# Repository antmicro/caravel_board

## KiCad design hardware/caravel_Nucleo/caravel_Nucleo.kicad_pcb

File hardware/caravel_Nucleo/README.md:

# Caravel Nucleo

### Overview

This repository contains open hardware design files for a expansion board compatible with [STM32 Nucleo-144 boards](https://www.st.com/en/evaluation-tools/stm32-nucleo-boards.html).\
This board connects IO signals from the STM32 MCU located on the Nucleo-144 board to an open hardware [Caravel](https://github.com/efabless/caravel_board).\
The Caravel breakout board allows testing ASIC designs prepared for Multi Project Wafer (MPW) shuttles and fabricated with one of the available open Process Design Kits (PDKs).

You can learn more about Open Shuttle Program by visiting this [link](https://efabless.com/open_shuttle_program).

The Caravel Nucleo board routes the interfaces from Caravel and provides the necessary power buses.
The design files were prepared in KiCad 6. This design is currently a Work in Progress (WiP).

## Project structure

The main repository directory contains KiCad PCB project files, and a README.
The remaining files are stored in the following directories:

* `lib` - contains the KiCad 6 component libraries
* `doc` - contains generated schematics and other documentation
* `img` - contains graphics for this README

## Key features

* Caravel-breakout testbed slot with optional FlexyPins
* `ST morpho` compatible
* USB for MPRJ SPI/UART debug
* SPI Flash connected to Caravel and Morpho connector
* Dedicated 10MHz oscillator
* Dual LDO with fixed and I2C controlled feedback (selectable)

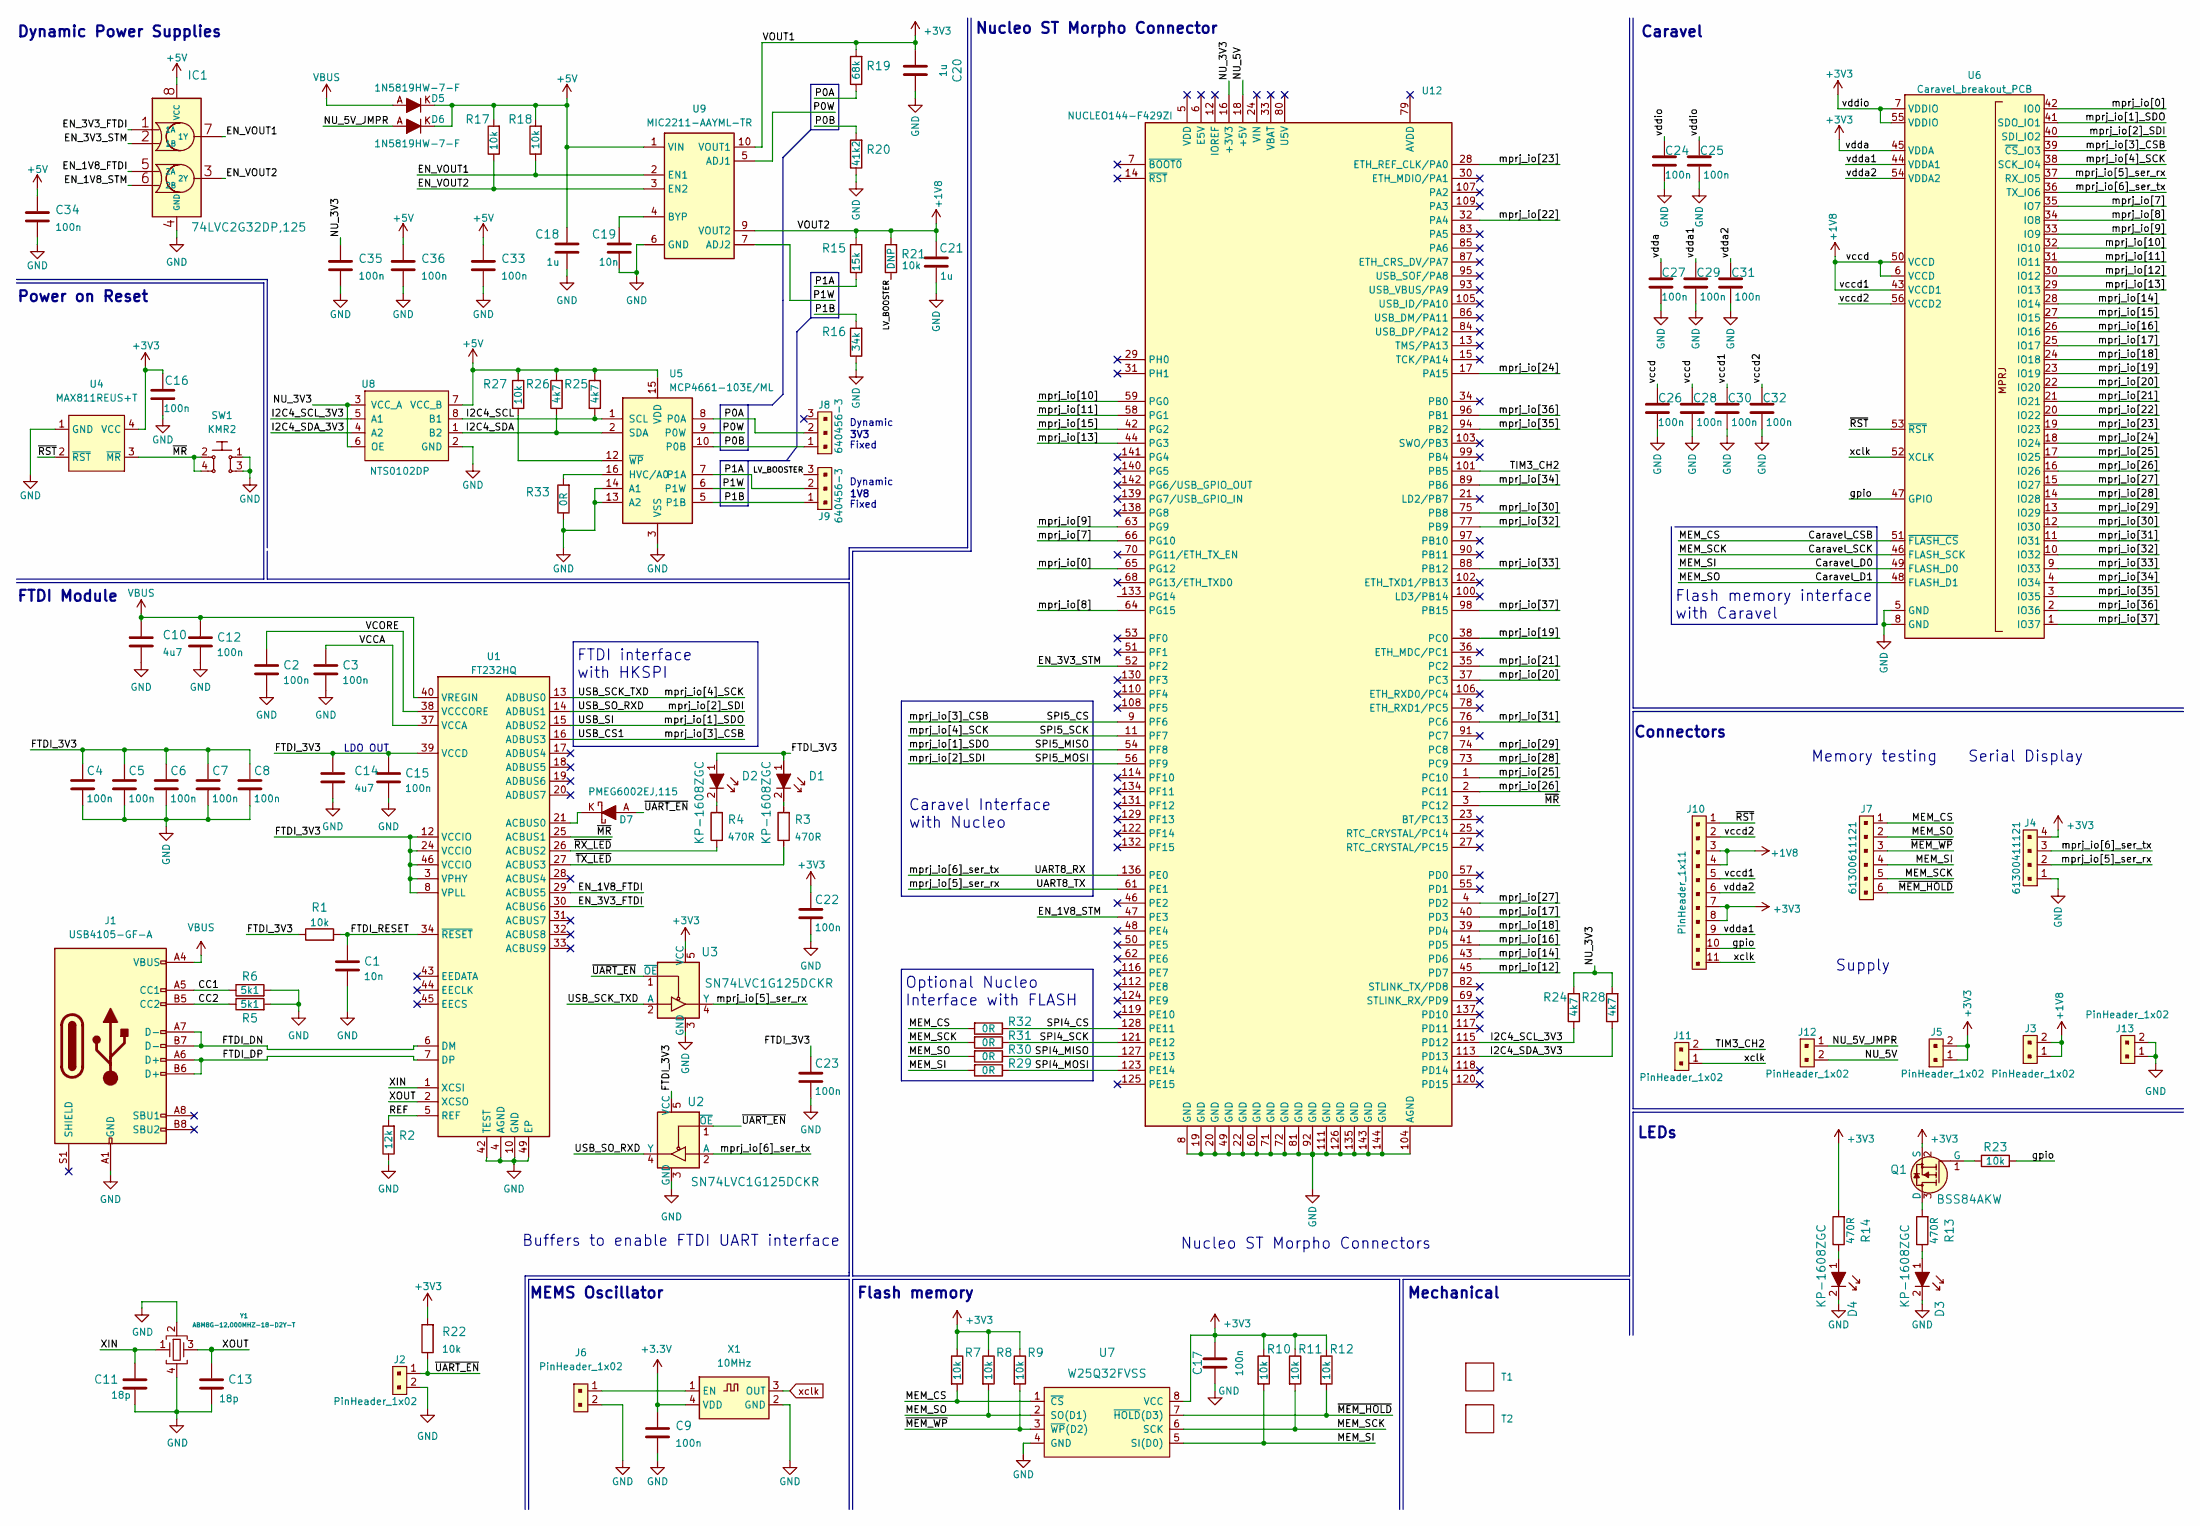
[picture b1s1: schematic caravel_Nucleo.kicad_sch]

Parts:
C1, C19: C_10n_0603; 0603-cap; MPN 06031C103JAT2A
C2, C3, C4, C5, C6, C7, C8, C9, C12, C15, C16, C17, C22, C23, C24, C25, C26, C27, C28, C29, C30, C31, C32, C33, C34, C35, C36: C_100n_0603; 0603-cap; MPN 0603YC104KAZ2A
C10, C14: C_4u7_0603; 0603-cap; MPN C1608X5R1V475M080AC
C11, C13: C_18p_0603; 0603-cap; MPN C0603C180J5GACTU
C18, C20, C21: C_1u_0603; 0603-cap; MPN 0603YD105KAT2A
D1, D2, D3, D4: KP-1608ZGC; LED_0603; MPN KP-1608EC
D5, D6: 1N5819HW-7-F; SOD-123; MPN 1N5819HW-7-F
D7: PMEG6002EJ,115; SOD-323F; MPN PMEG6002EJ,115
IC1: 74LVC2G32DP,125; TSSOP-8_W3mm; MPN 74LVC2G32DP,125
J1: USB4105-GF-A; GCT_USB4105-GF-A; MPN USB4105-GF-A
J2, J3, J5, J6, J11, J12, J13: PinHeader_1x02; PinHeader_1x2_P2.54mm; MPN M20-9990246
J4: 61300411121; PinHeader_1x4_P2.54mm_Drill1.02mm; MPN 61300411121
J7: 61300611121; MPN 61300611121
J8, J9: 640456-3; PinHeader_1x3_P2.54_Drill1.1mm; MPN 640456-3
J10: PinHeader_1x11; PinHeader_1x11_P2.54_Vertical; MPN 6-146280-1
Q1: BSS84AKW; SOT-323; MPN BSS84AKW,115
R1, R7, R8, R9, R10, R11, R12, R17, R18, R21, R22, R23, R27: R_10k_0603; 0603-res; MPN CR0603-JW-103ELF
R2: R_12k_0603; 0603-res; MPN CR0603-FX-1202ELF
R3, R4, R13, R14: R_470R_0603; 0603-res; MPN CR0603-JW-471GLF
R5, R6: R_5k1_0603; 0603-res; MPN CRCW06035K10FKEA
R15: R_15k_0603; 0603-res; MPN CR0603-FX-1502ELF
R16: R_34k_0603; 0603-res; MPN ERJ-3EKF3402V
R19: R_68k_0603; 0603-res; MPN MC0063W0603168K
R20: R_41k2_0603; 0603-res; MPN CRCW060341K2FKEA
R24, R25, R26, R28: R_4k7_0603; 0603-res; MPN CR0603-FX-4701ELF
R29, R30, R31, R32, R33: R_0R_0603; 0603-res; MPN CR0603-J/-000ELF
SW1: KMR2; SW_SPST_4.2x2.8; MPN KMR211NGLFS
T1: efabless_logo; logo
T2: efabless_logo
U1: FT232HQ; QFN-48-1EP_8x8mm_P0.5mm_EP6.2x6.2mm_FT232HQ_marking; MPN FT232HQ-TRAY
U2, U3: SN74LVC1G125DCKR; SOT-353; MPN SN74LVC1G125DCKR
U4: MAX811REUS+T; SOT-143-4; MPN MAX811REUS+T
U5: MCP4661-103E/ML; QFN-16_EP_4x4_Pitch0.65mm; MPN MCP4661103E/ML
U6: Caravel_breakout_PCB; caravel_breakout
U7: W25Q32FVSS; SOIC127P790X216-8N; MPN W25Q32FVSSIG
U8: NTS0102DP; TSSOP-8_W3mm; MPN NTS0102DP
U9: MIC2211-AAYML-TR; DFN-10-1EP_3x3mm; MPN MIC2211-AAYML-TR
U12: NUCLEO144-F429ZI; ST_Morpho_Connectors_144; MPN NUCLEO-F429ZI
X1: ECS-2520MVLC-100-BN-TR; Oscillator_SMD_ECS_2520MV-xxx-xx-4Pin_2.5x2.0mm; MPN ECS-2520MVLC-100-BN-TR
Y1: ABM8G-12.000MHZ-18-D2Y-T; KX-7; MPN ABM8G-12.000MHZ-18-D2Y-T

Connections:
+1V8: C21.1, C26.2, C28.2, C30.2, J3.1, J3.2, J10.3, J10.4, J10.5, R15.2, R21.2, U6.6 (VCCD), U6.43 (VCCD1), U6.50 (VCCD), U9.9 (VOUT2)
+5V: C18.1, C33.1, C34.1, C36.1, D5.K, D6.K, IC1.8 (VCC), R17.2, R18.2, R25.2, R26.2, R27.1, U5.15 (VDD), U8.7 (VCC_B), U9.1 (VIN)
/CC1: J1.A5 (CC1), R6.1
/CC2: J1.B5 (CC2), R5.1
/Caravel_CSB: J7.1, R7.2, R32.2, U6.51 (~FLASH_CS), U7.1 (~CS)
/Caravel_D0: J7.4, R10.2, R29.2, U6.49 (FLASH_D0), U7.5 (SI(D0))
/Caravel_D1: J7.2, R8.2, R30.2, U6.48 (FLASH_D1), U7.2 (SO(D1))
/Caravel_SCK: J7.5, R11.2, R31.2, U6.46 (FLASH_SCK), U7.6 (SCK)
/EN_1V8_FTDI: IC1.5 (2A), U1.29 (ACBUS5)
/EN_1V8_STM: IC1.6 (2B), U12.47 (PE3)
/EN_3V3_FTDI: IC1.1 (1A), U1.30 (ACBUS6)
/EN_3V3_STM: IC1.2 (1B), U12.52 (PF2)
/EN_VOUT1: IC1.7 (1Y), R18.1, U9.2 (EN1)
/EN_VOUT2: IC1.3 (2Y), R17.1, U9.3 (EN2)
/FTDI_3V3: C4.1, C5.1, C6.1, C7.1, C8.1, C14.1, C15.2, C23.1, D1.1, D2.1, R1.1, U1.3 (VPHY), U1.8 (VPLL), U1.12 (VCCIO), U1.24 (VCCIO), U1.39 (VCCD), U1.46 (VCCIO), U2.5 (VCC)
/FTDI_DN: J1.A7 (D-), J1.B7 (D-), U1.6 (DM)
/FTDI_DP: J1.A6 (D+), J1.B6 (D+), U1.7 (DP)
/FTDI_RESET: C1.1, R1.2, U1.34 (~RESET)
/I2C4_SCL: R25.1, U5.1 (SCL), U8.8 (B1)
/I2C4_SCL_3V3: R24.1, U8.5 (A1), U12.115 (PD12)
/I2C4_SDA: R26.1, U5.2 (SDA), U8.1 (B2)
/I2C4_SDA_3V3: R28.1, U8.4 (A2), U12.113 (PD13)
/LV_BOOSTER: J9.3, R21.1
/NU_3V3: C35.1, R24.2, R28.2, U8.3 (VCC_A), U8.6 (OE), U12.16 (+3V3)
/NU_5V: J12.2, U12.18 (+5V)
/NU_5V_JMPR: D6.A, J12.1
/P0A: J8.2, R19.1, U5.8 (P0A)
/P0B: J8.1, R20.2, U5.10 (P0B)
/P0W: U5.9 (P0W), U9.5 (ADJ1)
/P1A: J9.2, R15.1, U5.7 (P1A)
/P1B: J9.1, R16.2, U5.5 (P1B)
/P1W: U5.6 (P1W), U9.7 (ADJ2)
/REF: R2.2, U1.5 (REF)
/SPI4_CS: R32.1, U12.128 (PE11)
/SPI4_MISO: R30.1, U12.127 (PE13)
/SPI4_MOSI: R29.1, U12.123 (PE14)
/SPI4_SCK: R31.1, U12.121 (PE12)
/SPI5_CS: U1.16 (ADBUS3), U6.39 (~CS_IO3), U12.9 (PF6)
/SPI5_MISO: U1.15 (ADBUS2), U6.41 (SDO_IO1), U12.54 (PF8)
/SPI5_MOSI: U1.14 (ADBUS1), U2.4 (Y), U6.40 (SDI_IO2), U12.56 (PF9)
/SPI5_SCK: U1.13 (ADBUS0), U3.2 (A), U6.38 (SCK_IO4), U12.11 (PF7)
/TIM3_CH2: J11.2, U12.101 (PB5)
/UART8_RX: J4.3, U2.2 (A), U6.36 (TX_IO6), U12.136 (PE0)
/UART8_TX: J4.2, U3.4 (Y), U6.37 (RX_IO5), U12.61 (PE1)
/VCCA: C3.2, U1.37 (VCCA)
/VCORE: C2.2, U1.38 (VCCCORE)
/XIN: C11.1, U1.1 (XCSI), Y1.1
/XOUT: C13.1, U1.2 (XCSO), Y1.3
/gpio: J10.10, R23.2, U6.47 (GPIO)
/mprj_io[0]: U6.42 (IO0), U12.65 (PG12)
/mprj_io[7]: U6.35 (IO7), U12.66 (PG10)
/mprj_io[8]: U6.34 (IO8), U12.64 (PG15)
/mprj_io[9]: U6.33 (IO9), U12.63 (PG9)
/mprj_io[10]: U6.32 (IO10), U12.59 (PG0)
/mprj_io[11]: U6.31 (IO11), U12.58 (PG1)
/mprj_io[12]: U6.30 (IO12), U12.45 (PD7)
/mprj_io[13]: U6.29 (IO13), U12.44 (PG3)
/mprj_io[14]: U6.28 (IO14), U12.43 (PD6)
/mprj_io[15]: U6.27 (IO15), U12.42 (PG2)
/mprj_io[16]: U6.26 (IO16), U12.41 (PD5)
/mprj_io[17]: U6.25 (IO17), U12.40 (PD3)
/mprj_io[18]: U6.24 (IO18), U12.39 (PD4)
/mprj_io[19]: U6.23 (IO19), U12.38 (PC0)
/mprj_io[20]: U6.22 (IO20), U12.37 (PC3)
/mprj_io[21]: U6.21 (IO21), U12.35 (PC2)
/mprj_io[22]: U6.20 (IO22), U12.32 (PA4)
/mprj_io[23]: U6.19 (IO23), U12.28 (ETH_REF_CLK/PA0)
/mprj_io[24]: U6.18 (IO24), U12.17 (PA15)
/mprj_io[25]: U6.17 (IO25), U12.1 (PC10)
/mprj_io[26]: U6.16 (IO26), U12.2 (PC11)
/mprj_io[27]: U6.15 (IO27), U12.4 (PD2)
/mprj_io[28]: U6.14 (IO28), U12.73 (PC9)
/mprj_io[29]: U6.13 (IO29), U12.74 (PC8)
/mprj_io[30]: U6.12 (IO30), U12.75 (PB8)
/mprj_io[31]: U6.11 (IO31), U12.76 (PC6)
/mprj_io[32]: U6.10 (IO32), U12.77 (PB9)
/mprj_io[33]: U6.9 (IO33), U12.88 (PB12)
/mprj_io[34]: U6.4 (IO34), U12.89 (PB6)
/mprj_io[35]: U6.3 (IO35), U12.94 (PB2)
/mprj_io[36]: U6.2 (IO36), U12.96 (PB1)
/mprj_io[37]: U6.1 (IO37), U12.98 (PB15)
/vccd2: C32.2, J10.2, U6.56 (VCCD2)
/vdda1: C29.2, J10.9, U6.44 (VDDA1)
/vdda2: C31.2, J10.6, U6.54 (VDDA2)
/~MEM_HOLD: J7.6, R12.2, U7.7 (~HOLD(D3))
/~MEM_WP: J7.3, R9.2, U7.3 (~WP(D2))
/~MR: SW1.2, SW1.4, U1.25 (ACBUS1), U4.3 (~MR), U12.3 (PC12)
/~RST: J10.1, U4.2 (~RST), U6.53 (~RST)
/~RX_LED: R4.1, U1.26 (ACBUS2)
/~TX_LED: R3.1, U1.27 (ACBUS3)
/~UART_EN: D7.A, J2.1, R22.1, U2.1 (~OE), U3.1 (~OE)
AGND: C1.2, C2.1, C3.1, C4.2, C5.2, C6.2, C7.2, C8.2, C9.1, C10.2, C11.2, C12.1, C13.2, C14.2, C15.1, C16.2, C17.2, C18.2, C19.1, C20.2, C21.2, C22.2, C23.2, C24.1, C25.1, C26.1, C27.1, C28.1, C29.1, C30.1, C31.1, C32.1, C33.2, C34.2, C35.2, C36.2, D3.2, D4.2, IC1.4 (GND), J1.A1 (GND), J1.A12 (GND), J1.B1 (GND), J1.B12 (GND), J2.2, J4.1, J6.2, J13.1, J13.2, R2.1, R5.2, R6.2, R16.1, R20.1, R33.1, SW1.1, SW1.3, U1.4 (AGND), U1.9 (AGND), U1.10 (GND), U1.11 (GND), U1.22 (GND), U1.23 (GND), U1.35 (GND), U1.36 (GND), U1.41 (AGND), U1.42 (TEST), U1.47 (GND), U1.48 (GND), U1.49 (EP), U2.3 (GND), U3.3 (GND), U4.1 (GND), U5.3 (VSS), U5.4 (VSS), U5.13 (A2), U5.14 (A1), U6.5 (GND), U6.8 (GND), U7.4 (GND), U8.2 (GND), U9.6 (GND), U9.11 (EP), U12.8 (GND), U12.19 (GND), U12.20 (GND), U12.22 (GND), U12.49 (GND), U12.60 (GND), U12.71 (GND), U12.72 (GND), U12.81 (GND), U12.92 (GND), U12.104 (AGND), U12.111 (GND), U12.126 (GND), U12.135 (GND), U12.143 (GND), U12.144 (GND), X1.2 (GND), Y1.2, Y1.4
unnamed: C19.2, U9.4 (BYP)
unnamed: D1.2, R3.2
unnamed: D2.2, R4.2
unnamed: D3.1, R13.1
unnamed: D4.1, R14.1
unnamed: D7.K, U1.21 (ACBUS0)
unnamed: J6.1, X1.1 (EN)
unnamed: Q1.1 (G), R23.1
unnamed: Q1.3 (D), R13.2
unnamed: R27.2, U5.12 (~WP)
unnamed: R33.2, U5.16 (HVC/A0)
VBUS: C10.1, C12.2, D5.A, J1.A4 (VBUS), J1.A9 (VBUS), J1.B4 (VBUS), J1.B9 (VBUS), U1.40 (VREGIN)
xclk: J10.11, J11.1, U6.52 (XCLK), X1.3 (OUT)

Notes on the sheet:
Connectors
Caravel Interface with Nucleo
3V3
Flash memory
MEMS Oscillator
Serial Display
Power on Reset
FTDI Module
LEDs
Memory testing
LDO OUT
Optional Nucleo Interface with FLASH
Caravel
FTDI interface with HKSPI
Dynamic Fixed
1V8
Mechanical
Nucleo ST Morpho Connectors
Supply
Flash memory interface with Caravel
Buffers to enable FTDI UART interface
Dynamic Power Supplies
Nucleo ST Morpho Connector

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
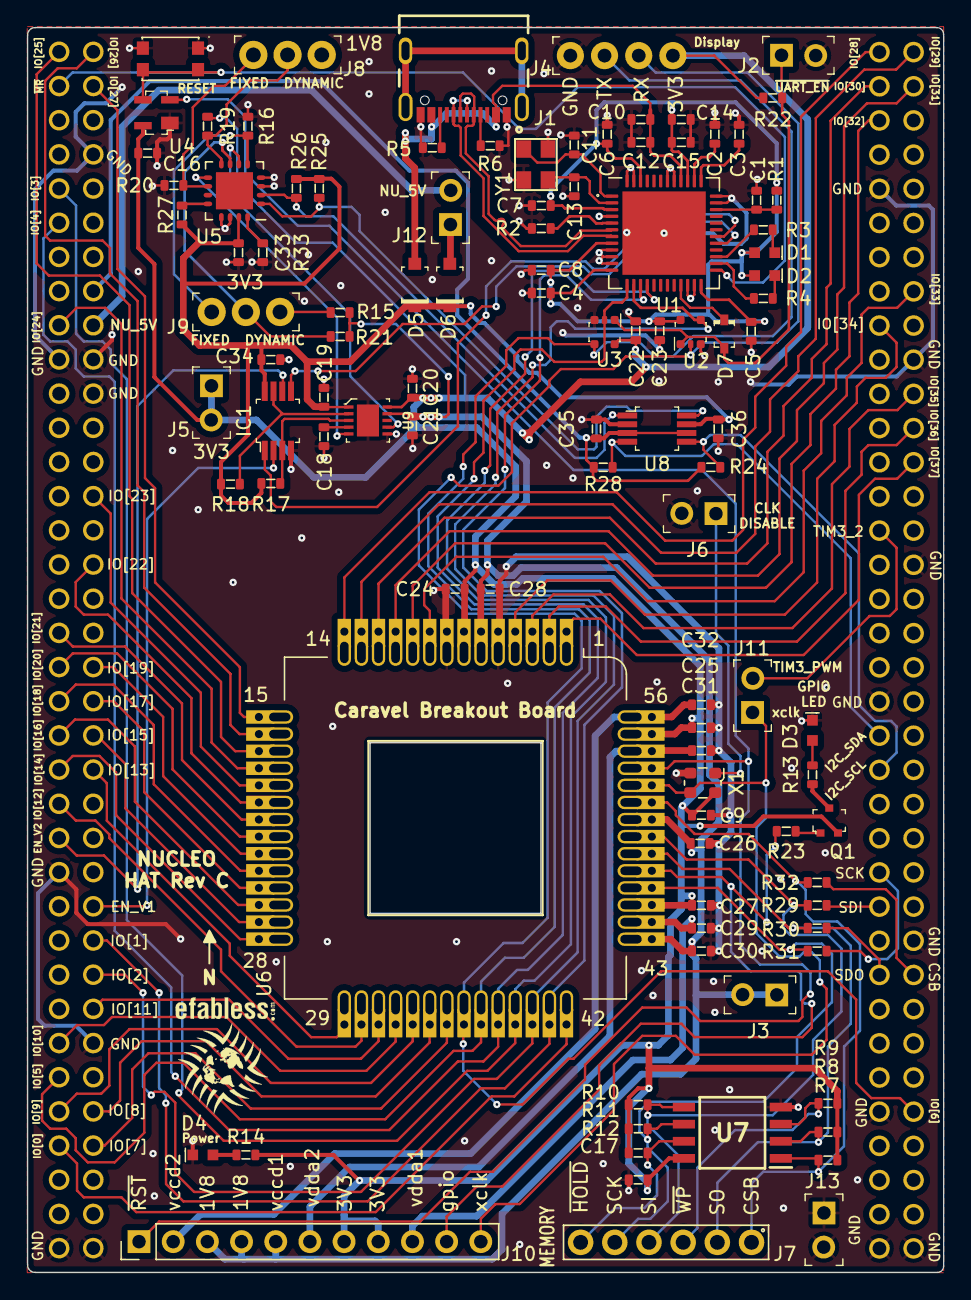
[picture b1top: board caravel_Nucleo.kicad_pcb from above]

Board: 4 copper layers, 68.1 x 92.5 mm, 106 parts (0 on the bottom side), 106 nets.

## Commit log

2022-12-19 Move docs to doc folder, remove datasheets
2022-12-19 Cleanup
2022-12-19 Adjust divider, add 1V8 LV option
2022-12-19 Annotate parts on schematic
2022-12-19 Substituted all components from main schematic sheet except Nucleo connector
2022-12-19 Update PCB components
2022-12-19 Add vizualization to the img folder
2022-12-19 Replace components to Antmicro library ones
2022-12-19 Finished changing symbols to antmicro global library
2022-12-19 Simplfy power supply
2022-12-19 Isolate FTDI scheamtic
2022-12-19 Tidy up schematic connections
2022-12-19 Add readme
2022-12-19 Move components to local library
2022-12-19 Rework FTDI sheet, begin improving main schematic sheet
2022-12-19 Further connection tidy up, regroup components in to logical blocks, add gpio LED PMOS, add possiblility to supply device with USB VBUS
2022-12-19 Update FTDI symbol
2022-12-19 Add UART_EN signal short protection for FTDI, add OR gate for enabling LDO
2022-12-19 Add missing decoupling, fix passive components size
2022-12-19 Add on schematic I2C logic level translator, add missing decoupling, change J12 voltage assigment
2022-12-19 Update local libraries. Remove library bak file
2022-12-19 Update components in schematic. Annotation
2022-12-19 Update Efabless logo on schematics
2022-12-19 Update FTDI footprint on PCB
2022-12-19 Initial PCB placement, start routing
2022-12-19 Route FTDI and corresponding interfaces, route dynamic power supply, connect remainig signals
2022-12-19 Finish routing PCB, add I2C logic level translator, fix layer stackup, clear DRC, tidy up silkscreen
2022-12-19 Update STM Morpho 3D model
2022-12-19 Optimize GND via placment
2022-12-19 Update PCB with new components
2022-12-19 Update Efabless logo on PCB

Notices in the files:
parts and their libraries:
License: MIT
